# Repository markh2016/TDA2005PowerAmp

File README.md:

# TDA2005PowerAmp
Small Bridge mode power amp using TDA2005  
A nice little or project  and where  you could create  your own very market  for these  and work from home 
Enjoy  !! 

MD Harrington  Kent  

London South east 

DOB 20-01-1964 

Self taught via the net using open source 

Kicad  and excellent PCB schematic design package  that wonbt cost you an arm and a leg 
Ideal for getting yourselves up and running

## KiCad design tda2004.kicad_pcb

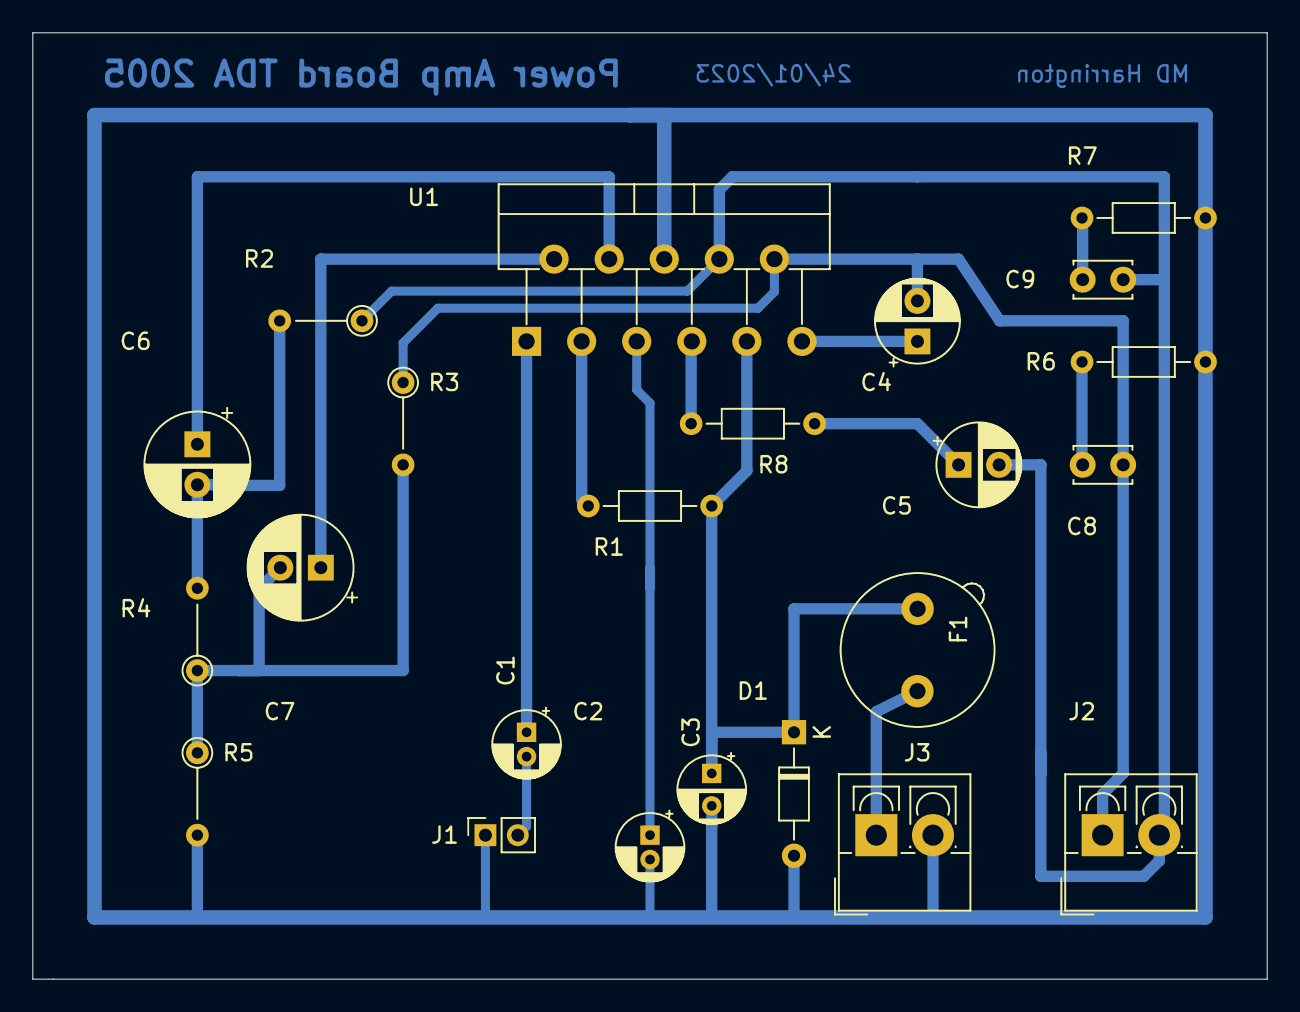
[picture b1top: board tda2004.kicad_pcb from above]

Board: 2 copper layers, 76.2 x 58.4 mm, 23 parts (0 on the bottom side), 18 nets.

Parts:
C1, C2: 2.2uf; CP_Radial_D4.0mm_P1.50mm
C3: 10uf; CP_Radial_D4.0mm_P2.00mm
C4, C5: 100uf; CP_Radial_D5.0mm_P2.50mm
C6, C7: 220uf; CP_Radial_D6.3mm_P2.50mm
C8, C9: 0.1uf; C_Disc_D3.4mm_W2.1mm_P2.50mm
D1: 1N5401; D_DO-34_SOD68_P7.62mm_Horizontal
F1: Fuse_Small; Fuseholder_TR5_Littelfuse_No560_No460
J1: RcaSocketCon; PinSocket_1x02_P2.00mm_Vertical
J2: Output; TerminalBlock_4Ucon_1x02_P3.50mm_Vertical
J3: DC Power IN; TerminalBlock_4Ucon_1x02_P3.50mm_Vertical
R1: 120k; R_Axial_DIN0204_L3.6mm_D1.6mm_P7.62mm_Horizontal
R2: 2k; R_Axial_DIN0204_L3.6mm_D1.6mm_P5.08mm_Vertical
R3: 1k; R_Axial_DIN0204_L3.6mm_D1.6mm_P5.08mm_Vertical
R4, R5: 12R; R_Axial_DIN0204_L3.6mm_D1.6mm_P5.08mm_Vertical
R6, R7: 1R; R_Axial_DIN0204_L3.6mm_D1.6mm_P7.62mm_Horizontal
R8: 0R0; R_Axial_DIN0204_L3.6mm_D1.6mm_P7.62mm_Horizontal
U1: TDA2005; TO-220-11_P3.4x5.08mm_StaggerOdd_Lead4.85mm_Vertical

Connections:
GNDREF: C2.2, C3.2, D1.2, J1.1, J3.2, R5.2, R6.2, R7.2, U1.6
unnamed: C1.1, U1.1
unnamed: C1.2, J1.2
unnamed: C2.1, U1.5
unnamed: C4.1, U1.11
unnamed: C4.2, C8.1, J2.1, R3.1, U1.10
unnamed: C5.1, R8.1
unnamed: C5.2, C9.1, J2.2, R2.1, U1.8
unnamed: C6.1, U1.4
unnamed: C6.2, R2.2, R4.2
unnamed: C7.1, U1.2
unnamed: C7.2, R3.2, R4.1, R5.1
unnamed: C8.2, R6.1
unnamed: C9.2, R7.1
unnamed: F1.1, J3.1
unnamed: R1.2, U1.3
unnamed: R8.2, U1.7
V+Max18vdc: C3.1, D1.1, F1.2, R1.1, U1.9
